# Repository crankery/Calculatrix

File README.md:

Stupid calculator based around the 6507.

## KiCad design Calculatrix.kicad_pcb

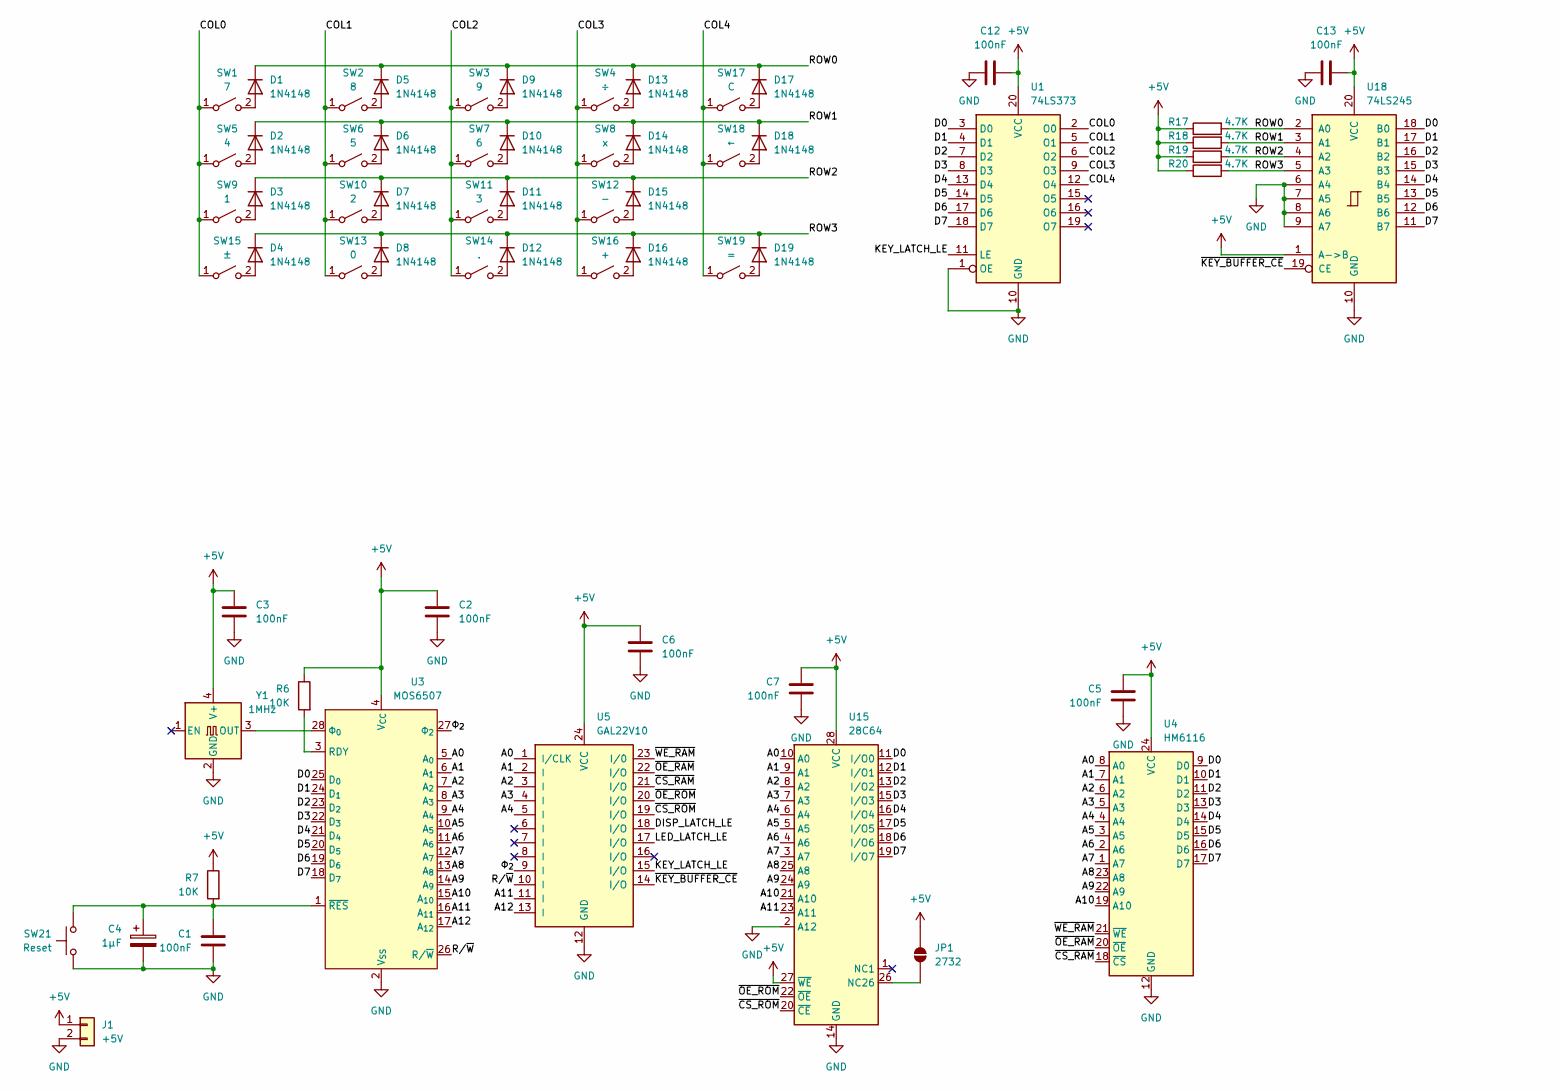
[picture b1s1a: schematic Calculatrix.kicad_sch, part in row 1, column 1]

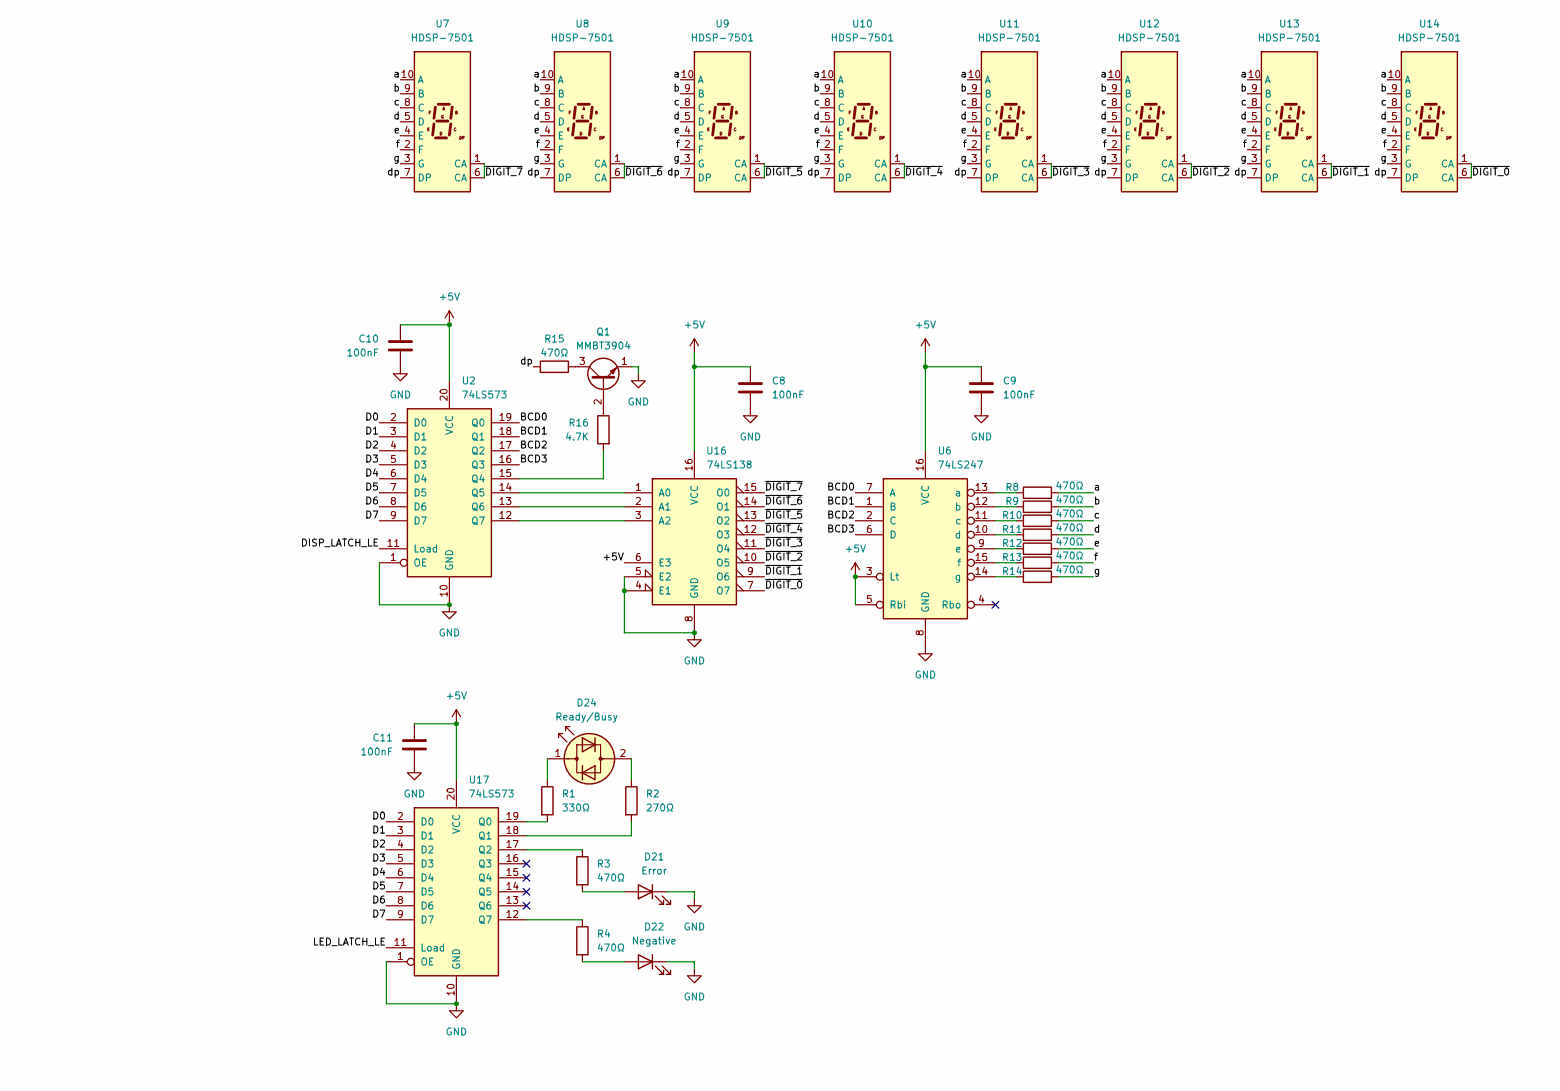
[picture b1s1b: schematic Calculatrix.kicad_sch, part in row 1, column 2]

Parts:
C1, C2, C3, C5, C6, C7, C8, C9, C10, C11, C12, C13: 100nF; C_1206_3216Metric
C4: 1µF; CP_Elec_4x5.3
D1, D2, D3, D4, D5, D6, D7, D8, D9, D10, D11, D12, D13, D14, D15, D16, D17, D18, D19: 1N4148; D_MiniMELF
D21: Error; LED_D3.0mm
D22: Negative; LED_Rectangular_W3.9mm_H1.8mm
D24: Ready/Busy; LED_D3.0mm_Clear
J1: +5V; JST_PH_S2B-PH-K_1x02_P2.00mm_Horizontal
JP1: 2732; SolderJumper-2_P1.3mm_Open_RoundedPad1.0x1.5mm
Q1: MMBT3904; SOT-23
R1: 330Ω; R_1206_3216Metric_Pad1.30x1.75mm_HandSolder
R2: 270Ω; R_1206_3216Metric_Pad1.30x1.75mm_HandSolder
R3, R4, R8, R9, R10, R11, R12, R13, R14, R15: 470Ω; R_1206_3216Metric_Pad1.30x1.75mm_HandSolder
R6, R7: 10K; R_1206_3216Metric_Pad1.30x1.75mm_HandSolder
R16, R17, R18, R19, R20: 4.7K; R_1206_3216Metric_Pad1.30x1.75mm_HandSolder
SW1: 7; SW_Cherry_MX_1.00u_PCB
SW2: 8; SW_Cherry_MX_1.00u_PCB
SW3: 9; SW_Cherry_MX_1.00u_PCB
SW4: ÷; SW_Cherry_MX_1.00u_PCB
SW5: 4; SW_Cherry_MX_1.00u_PCB
SW6: 5; SW_Cherry_MX_1.00u_PCB
SW7: 6; SW_Cherry_MX_1.00u_PCB
SW8: x; SW_Cherry_MX_1.00u_PCB
SW9: 1; SW_Cherry_MX_1.00u_PCB
SW10: 2; SW_Cherry_MX_1.00u_PCB
SW11: 3; SW_Cherry_MX_1.00u_PCB
SW12: -; SW_Cherry_MX_1.00u_PCB
SW13: 0; SW_Cherry_MX_1.00u_PCB
SW14: .; SW_Cherry_MX_1.00u_PCB
SW15: ±; SW_Cherry_MX_1.00u_PCB
SW16: +; SW_Cherry_MX_1.00u_PCB
SW17: C; SW_PUSH_6mm_H13mm
SW18: ←; SW_PUSH_6mm_H13mm
SW19: =; SW_Cherry_MX_1.00u_PCB
SW21: Reset; SW_Tactile_SPST_Angled_PTS645Vx31-2LFS
U1: 74LS373; SOIC-20W_7.5x12.8mm_P1.27mm
U2, U17: 74LS573; SOIC-20W_7.5x12.8mm_P1.27mm
U3: MOS6507; DIP-28_W15.24mm
U4: HM6116; DIP-24_W15.24mm-Split
U5: GAL22V10; DIP-24_W7.62mm
U6: 74LS247; DIP-16_W7.62mm
U7, U8, U9, U10, U11, U12, U13, U14: HDSP-7501; HDSP-A151
U15: 28C64; DIP-28_W15.24mm-Split
U16: 74LS138; SOIC-16_3.9x9.9mm_P1.27mm
U18: 74LS245; SOIC-20W_7.5x12.8mm_P1.27mm
Y1: 1MHz; Oscillator_SMD_EuroQuartz_XO53-4Pin_5.0x3.2mm_HandSoldering

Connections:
+5V: C2.1, C3.1, C5.1, C6.1, C7.1, C8.1, C9.1, C10.1, C11.1, C12.2, C13.2, J1.1, JP1.2 (B), R6.1, R7.1, R17.1, R18.1, R19.1, R20.1, U1.20 (VCC), U2.20 (VCC), U3.4 (V_{CC}), U4.24 (VCC), U5.24 (VCC), U6.3 (Lt), U6.5 (Rbi), U6.16 (VCC), U15.27 (~WE), U15.28 (VCC), U16.6 (E3), U16.16 (VCC), U17.20 (VCC), U18.1 (A->B), U18.20 (VCC), Y1.4 (V+)
/A0: U3.5 (A_{0}), U4.8 (A0), U5.1 (I/CLK), U15.10 (A0)
/A1: U3.6 (A_{1}), U4.7 (A1), U5.2 (I), U15.9 (A1)
/A2: U3.7 (A_{2}), U4.6 (A2), U5.3 (I), U15.8 (A2)
/A3: U3.8 (A_{3}), U4.5 (A3), U5.4 (I), U15.7 (A3)
/A4: U3.9 (A_{4}), U4.4 (A4), U5.5 (I), U15.6 (A4)
/A5: U3.10 (A_{5}), U4.3 (A5), U15.5 (A5)
/A6: U3.11 (A_{6}), U4.2 (A6), U15.4 (A6)
/A7: U3.12 (A_{7}), U4.1 (A7), U15.3 (A7)
/A8: U3.13 (A_{8}), U4.23 (A8), U15.25 (A8)
/A9: U3.14 (A_{9}), U4.22 (A9), U15.24 (A9)
/A10: U3.15 (A_{10}), U4.19 (A10), U15.21 (A10)
/A11: U3.16 (A_{11}), U5.11 (I), U15.23 (A11)
/A12: U3.17 (A_{12}), U5.13 (I)
/BCD0: U2.19 (Q0), U6.7 (A)
/BCD1: U2.18 (Q1), U6.1 (B)
/BCD2: U2.17 (Q2), U6.2 (C)
/BCD3: U2.16 (Q3), U6.6 (D)
/COL0: SW1.1 (A), SW5.1 (A), SW9.1 (A), SW15.1 (A), U1.2 (O0)
/COL1: SW2.1 (A), SW6.1 (A), SW10.1 (A), SW13.1 (A), U1.5 (O1)
/COL2: SW3.1 (A), SW7.1 (A), SW11.1 (A), SW14.1 (A), U1.6 (O2)
/COL3: SW4.1 (A), SW8.1 (A), SW12.1 (A), SW16.1 (A), U1.9 (O3)
/COL4: SW17.1 (A), SW18.1 (A), SW19.1 (A), U1.12 (O4)
/D0: U1.3 (D0), U2.2 (D0), U3.25 (D_{0}), U4.9 (D0), U15.11 (I/O0), U17.2 (D0), U18.18 (B0)
/D1: U1.4 (D1), U2.3 (D1), U3.24 (D_{1}), U4.10 (D1), U15.12 (I/O1), U17.3 (D1), U18.17 (B1)
/D2: U1.7 (D2), U2.4 (D2), U3.23 (D_{2}), U4.11 (D2), U15.13 (I/O2), U17.4 (D2), U18.16 (B2)
/D3: U1.8 (D3), U2.5 (D3), U3.22 (D_{3}), U4.13 (D3), U15.15 (I/O3), U17.5 (D3), U18.15 (B3)
/D4: U1.13 (D4), U2.6 (D4), U3.21 (D_{4}), U4.14 (D4), U15.16 (I/O4), U17.6 (D4), U18.14 (B4)
/D5: U1.14 (D5), U2.7 (D5), U3.20 (D_{5}), U4.15 (D5), U15.17 (I/O5), U17.7 (D5), U18.13 (B5)
/D6: U1.17 (D6), U2.8 (D6), U3.19 (D_{6}), U4.16 (D6), U15.18 (I/O6), U17.8 (D6), U18.12 (B6)
/D7: U1.18 (D7), U2.9 (D7), U3.18 (D_{7}), U4.17 (D7), U15.19 (I/O7), U17.9 (D7), U18.11 (B7)
/DISP_LATCH_LE: U2.11 (Load), U5.18 (I/O)
/KEY_LATCH_LE: U1.11 (LE), U5.15 (I/O)
/LED_LATCH_LE: U5.17 (I/O), U17.11 (Load)
/ROW0: D1.1 (K), D5.1 (K), D9.1 (K), D13.1 (K), D17.1 (K), R17.2, U18.2 (A0)
/ROW1: D2.1 (K), D6.1 (K), D10.1 (K), D14.1 (K), D18.1 (K), R18.2, U18.3 (A1)
/ROW2: D3.1 (K), D7.1 (K), D11.1 (K), D15.1 (K), R19.2, U18.4 (A2)
/ROW3: D4.1 (K), D8.1 (K), D12.1 (K), D16.1 (K), D19.1 (K), R20.2, U18.5 (A3)
/R/~W: U3.26 (R/~W), U5.10 (I)
/a: R8.2, U7.10 (A), U8.10 (A), U9.10 (A), U10.10 (A), U11.10 (A), U12.10 (A), U13.10 (A), U14.10 (A)
/b: R9.2, U7.9 (B), U8.9 (B), U9.9 (B), U10.9 (B), U11.9 (B), U12.9 (B), U13.9 (B), U14.9 (B)
/c: R10.2, U7.8 (C), U8.8 (C), U9.8 (C), U10.8 (C), U11.8 (C), U12.8 (C), U13.8 (C), U14.8 (C)
/d: R11.2, U7.5 (D), U8.5 (D), U9.5 (D), U10.5 (D), U11.5 (D), U12.5 (D), U13.5 (D), U14.5 (D)
/dp: R15.2, U7.7 (DP), U8.7 (DP), U9.7 (DP), U10.7 (DP), U11.7 (DP), U12.7 (DP), U13.7 (DP), U14.7 (DP)
/e: R12.2, U7.4 (E), U8.4 (E), U9.4 (E), U10.4 (E), U11.4 (E), U12.4 (E), U13.4 (E), U14.4 (E)
/f: R13.2, U7.2 (F), U8.2 (F), U9.2 (F), U10.2 (F), U11.2 (F), U12.2 (F), U13.2 (F), U14.2 (F)
/g: R14.2, U7.3 (G), U8.3 (G), U9.3 (G), U10.3 (G), U11.3 (G), U12.3 (G), U13.3 (G), U14.3 (G)
/~CS_RAM: U4.18 (~CS), U5.21 (I/O)
/~CS_ROM: U5.19 (I/O), U15.20 (~CE)
/~DIGIT_0: U14.1 (CA), U14.6 (CA), U16.7 (O7)
/~DIGIT_1: U13.1 (CA), U13.6 (CA), U16.9 (O6)
/~DIGIT_2: U12.1 (CA), U12.6 (CA), U16.10 (O5)
/~DIGIT_3: U11.1 (CA), U11.6 (CA), U16.11 (O4)
/~DIGIT_4: U10.1 (CA), U10.6 (CA), U16.12 (O3)
/~DIGIT_5: U9.1 (CA), U9.6 (CA), U16.13 (O2)
/~DIGIT_6: U8.1 (CA), U8.6 (CA), U16.14 (O1)
/~DIGIT_7: U7.1 (CA), U7.6 (CA), U16.15 (O0)
/~KEY_BUFFER_CE: U5.14 (I/O), U18.19 (CE)
/~OE_RAM: U4.20 (~OE), U5.22 (I/O)
/~OE_ROM: U5.20 (I/O), U15.22 (~OE)
/~WE_RAM: U4.21 (~WE), U5.23 (I/0)
/Φ_{2}: U3.27 (Φ_{2}), U5.9 (I)
GND: C1.2, C2.2, C3.2, C4.2, C5.2, C6.2, C7.2, C8.2, C9.2, C10.2, C11.2, C12.1, C13.1, D21.1 (K), D22.1 (K), J1.2, Q1.1 (E), SW21.1, U1.1 (OE), U1.10 (GND), U2.1 (OE), U2.10 (GND), U3.2 (V_{SS}), U4.12 (GND), U5.12 (GND), U6.8 (GND), U15.2 (A12), U15.14 (GND), U16.4 (E1), U16.5 (E2), U16.8 (GND), U17.1 (OE), U17.10 (GND), U18.6 (A4), U18.7 (A5), U18.8 (A6), U18.9 (A7), U18.10 (GND), Y1.2 (GND)
unnamed: D1.2 (A), SW1.2 (B)
unnamed: D2.2 (A), SW5.2 (B)
unnamed: D3.2 (A), SW9.2 (B)
unnamed: D4.2 (A), SW15.2 (B)
unnamed: D5.2 (A), SW2.2 (B)
unnamed: D6.2 (A), SW6.2 (B)
unnamed: D7.2 (A), SW10.2 (B)
unnamed: D8.2 (A), SW13.2 (B)
unnamed: D9.2 (A), SW3.2 (B)
unnamed: D10.2 (A), SW7.2 (B)
unnamed: D11.2 (A), SW11.2 (B)
unnamed: D12.2 (A), SW14.2 (B)
unnamed: D13.2 (A), SW4.2 (B)
unnamed: D14.2 (A), SW8.2 (B)
unnamed: D15.2 (A), SW12.2 (B)
unnamed: D16.2 (A), SW16.2 (B)
unnamed: D17.2 (A), SW17.2 (B)
unnamed: D18.2 (A), SW18.2 (B)
unnamed: D19.2 (A), SW19.2 (B)
unnamed: D21.2 (A), R3.2
unnamed: D22.2 (A), R4.2
unnamed: D24.2 (AK), R2.1
unnamed: D24.1 (KA), R1.1
unnamed: JP1.1 (A), U15.26 (NC26)
unnamed: Q1.2 (B), R16.1
unnamed: Q1.3 (C), R15.1
unnamed: R16.2, U2.15 (Q4)
unnamed: R6.2, U3.3 (RDY)
unnamed: C1.1, C4.1, R7.2, SW21.2, U3.1 (~RES)
unnamed: U3.28 (Φ_{0}), Y1.3 (OUT)
unnamed: R8.1, U6.13 (a)
unnamed: R9.1, U6.12 (b)
unnamed: R10.1, U6.11 (c)
unnamed: R11.1, U6.10 (d)
unnamed: R12.1, U6.9 (e)
unnamed: R13.1, U6.15 (f)
unnamed: R14.1, U6.14 (g)
unnamed: U2.14 (Q5), U16.1 (A0)
unnamed: U2.13 (Q6), U16.2 (A1)
unnamed: U2.12 (Q7), U16.3 (A2)
unnamed: R1.2, U17.19 (Q0)
unnamed: R2.2, U17.18 (Q1)
unnamed: R3.1, U17.17 (Q2)
unnamed: R4.1, U17.12 (Q7)

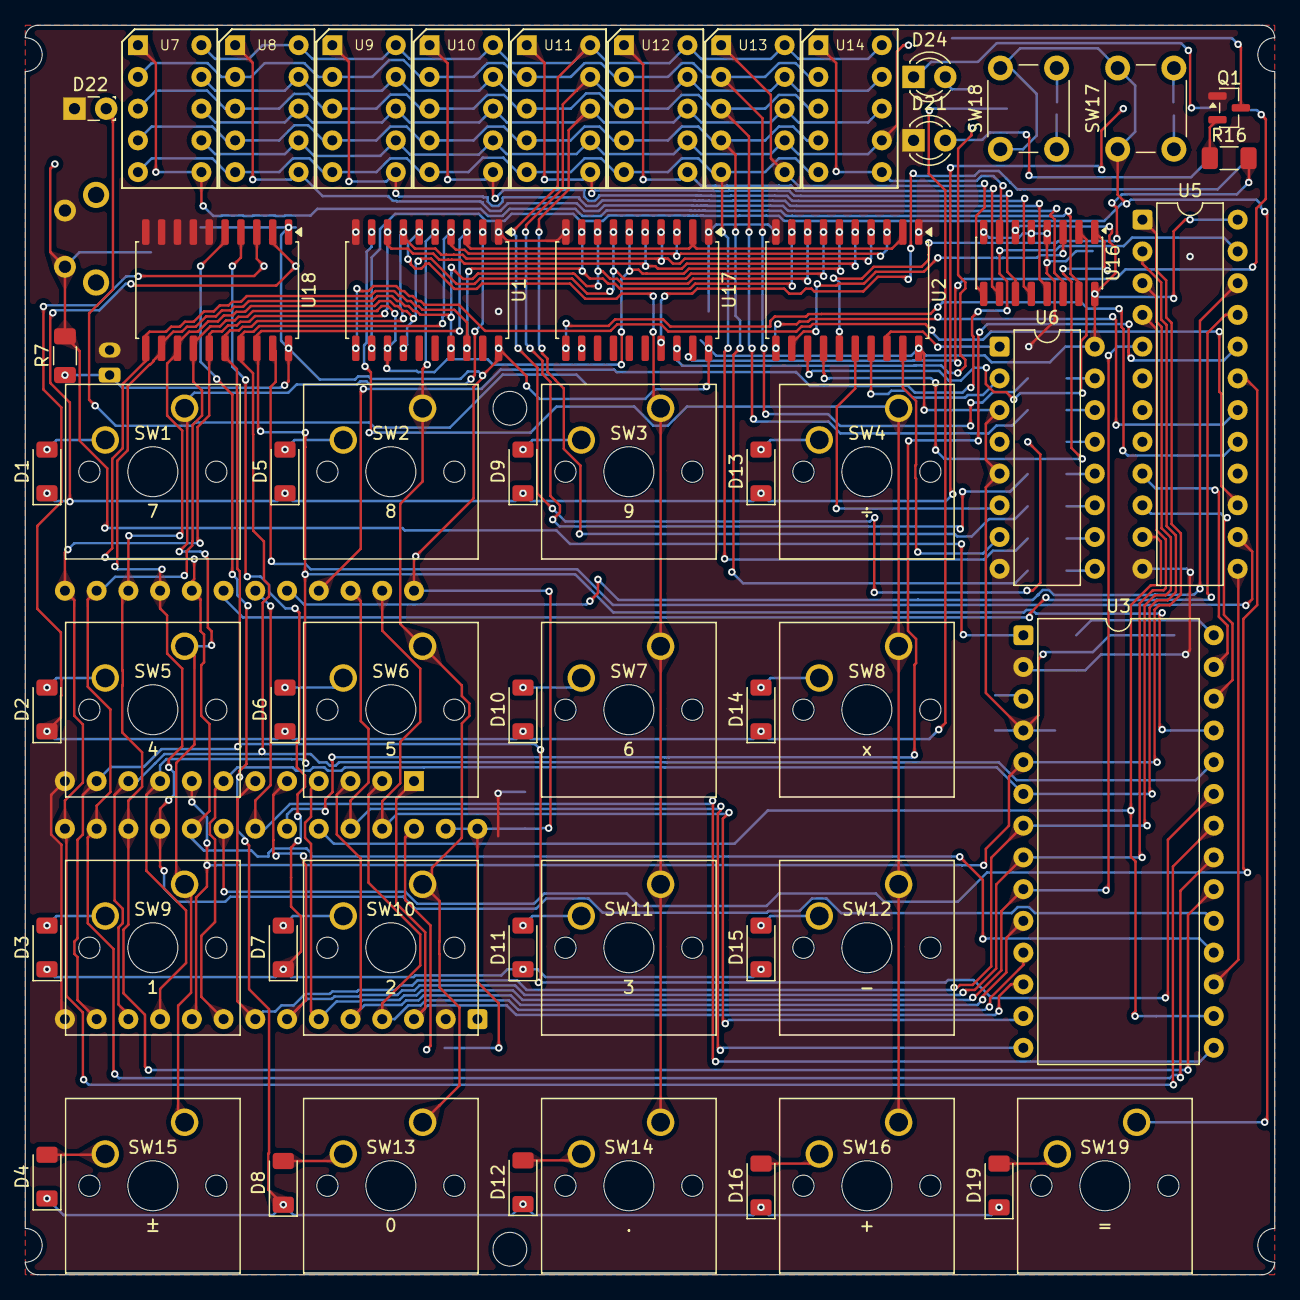
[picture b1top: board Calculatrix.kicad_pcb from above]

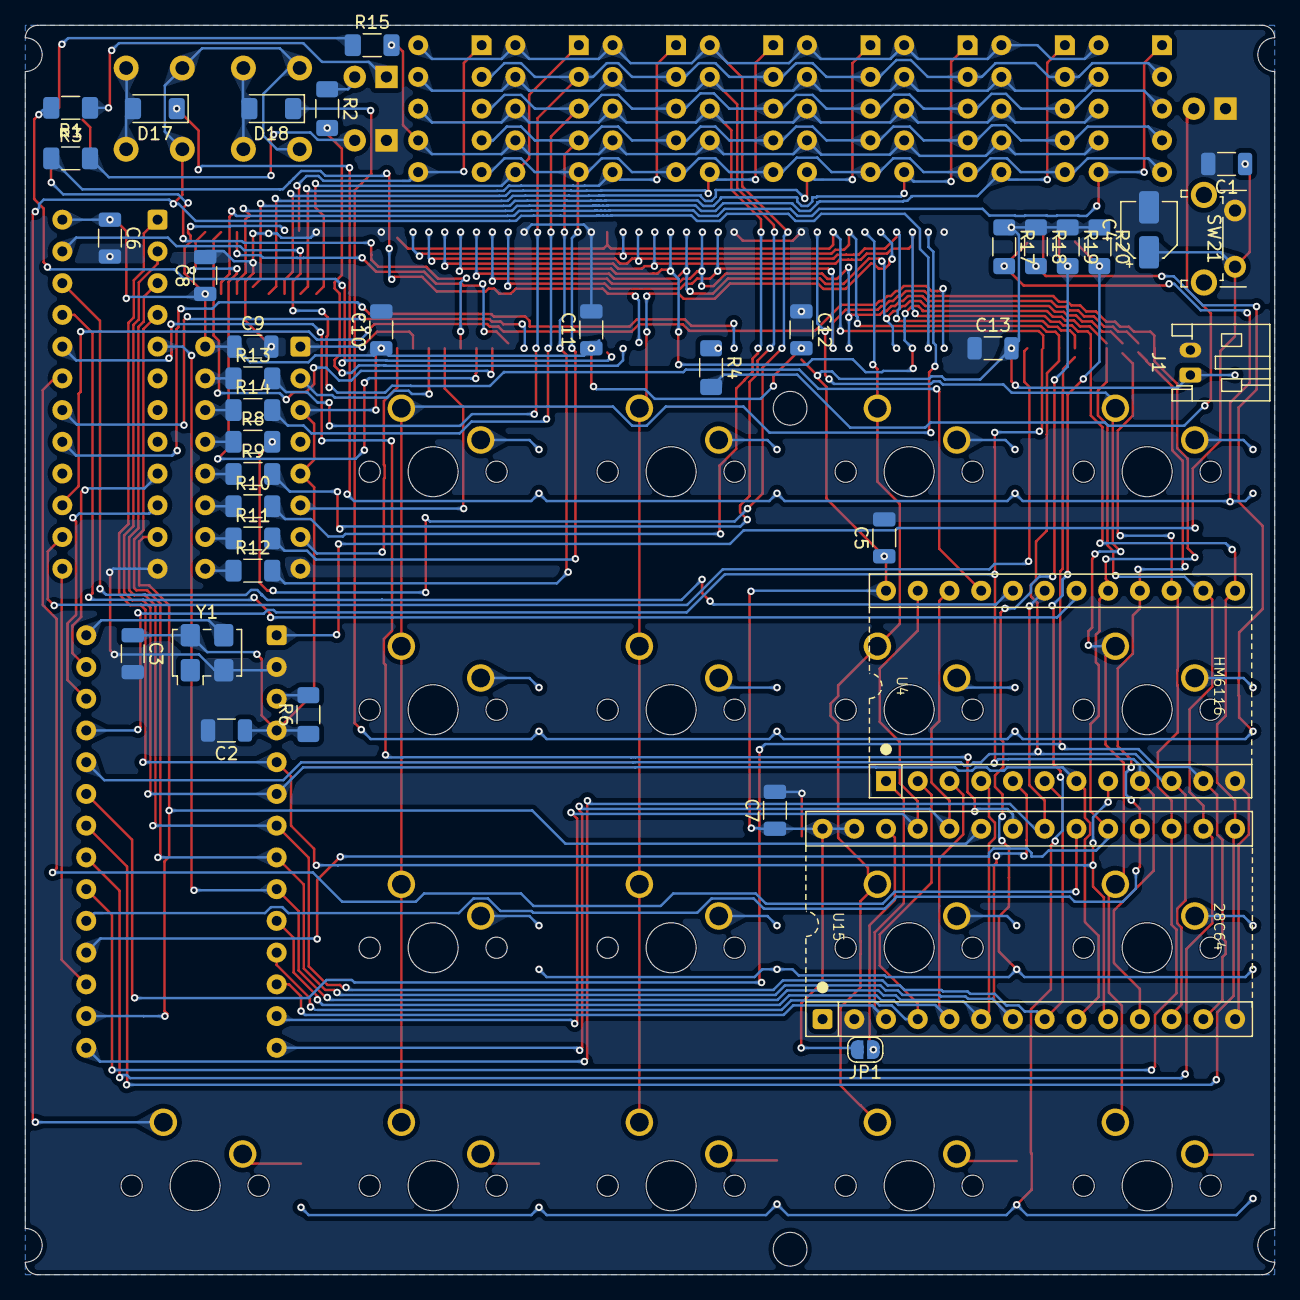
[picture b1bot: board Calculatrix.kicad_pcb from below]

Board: 2 copper layers, 100.0 x 100.0 mm, 96 parts (38 on the bottom side), 107 nets.

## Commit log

2026-05-06 Add project description to README
2026-05-06 remove files that should have been ignored (I did that all out of order)
2026-05-06 adding vasm
2026-05-07 update emu
2026-05-07 remove submodule
2026-05-07 remove submodules
2026-05-07 remove ds store
2026-05-07 move docs into docs
2026-05-07 remove test files
2026-05-07 remove 3 pin key switch model
2026-05-07 no submodules
2026-05-07 clean up
